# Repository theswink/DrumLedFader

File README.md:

# DrumLedFader
flash LED's when hitting the drums and do some more eye candy.

https://www.youtube.com/watch?v=Rv88M1jl1K8&t=31s&ab_channel=WilfredSwinkels

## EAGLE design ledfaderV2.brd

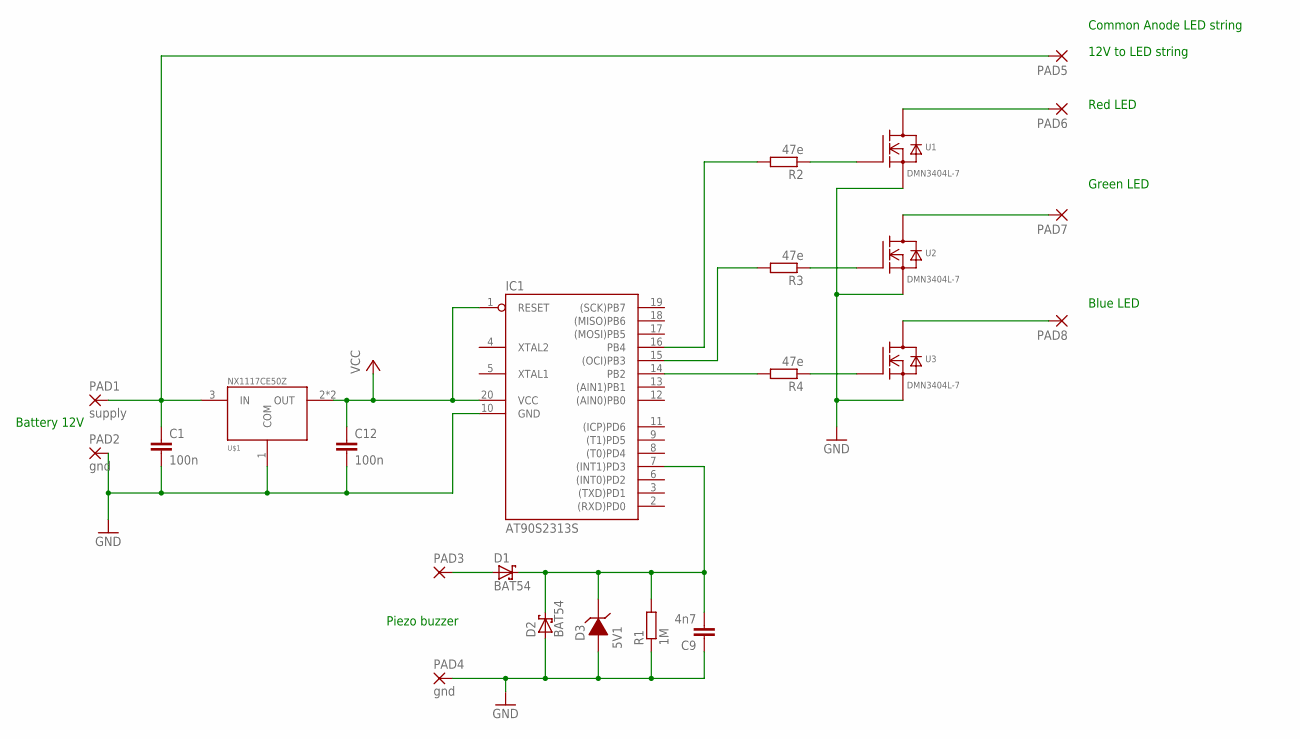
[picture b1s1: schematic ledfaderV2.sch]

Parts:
C1, C12: 100n; C1206
C9: 4n7; C1206
D1, D2: BAT54; SOT23
D3: 5V1; MINI-MELF
IC1: AT90S2313S; SO20L
PAD1: supply; SMD2,54-5,08
PAD2, PAD4: gnd; SMD2,54-5,08
PAD3, PAD5, PAD6, PAD7, PAD8: SMD5; SMD2,54-5,08
R1: 1M; M1206
R2, R3, R4: 47e; M1206
U1, U2, U3: DMN3404L-7; SOT95P235X112-3N; MPN DMN3404L-7
U$1: NX1117CE50Z; SOT223

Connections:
GND: C9.1, D2.1 (A), D3.1 (A), PAD4.1, R1.1, U1.2 (S), U2.2 (S), U3.2 (S)
unnamed: C1.1, PAD1.1, PAD5.1, U$1.3 (IN)
unnamed: C9.2, D1.3 (C), D2.3 (C), D3.2 (C), IC1.7 ((INT1)PD3), R1.2
unnamed: PAD6.1, U1.3 (D)
unnamed: PAD7.1, U2.3 (D)
unnamed: D1.1 (A), PAD3.1
unnamed: PAD8.1, U3.3 (D)
unnamed: R2.1, U1.1 (G)
unnamed: C1.2, C12.2, IC1.10 (GND), PAD2.1, U$1.1 (COM)
unnamed: R3.1, U2.1 (G)
unnamed: IC1.16 (PB4), R2.2
unnamed: IC1.15 ((OCI)PB3), R3.2
unnamed: IC1.14 (PB2), R4.2
unnamed: R4.1, U3.1 (G)
VCC: C12.1, IC1.1 (RESET), IC1.20 (VCC), U$1.2 (OUT), U$1.4 (OUT)

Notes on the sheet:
Battery 12V
12V to LED string
Red LED
Green LED
Blue LED
Common Anode LED string
Piezo buzzer

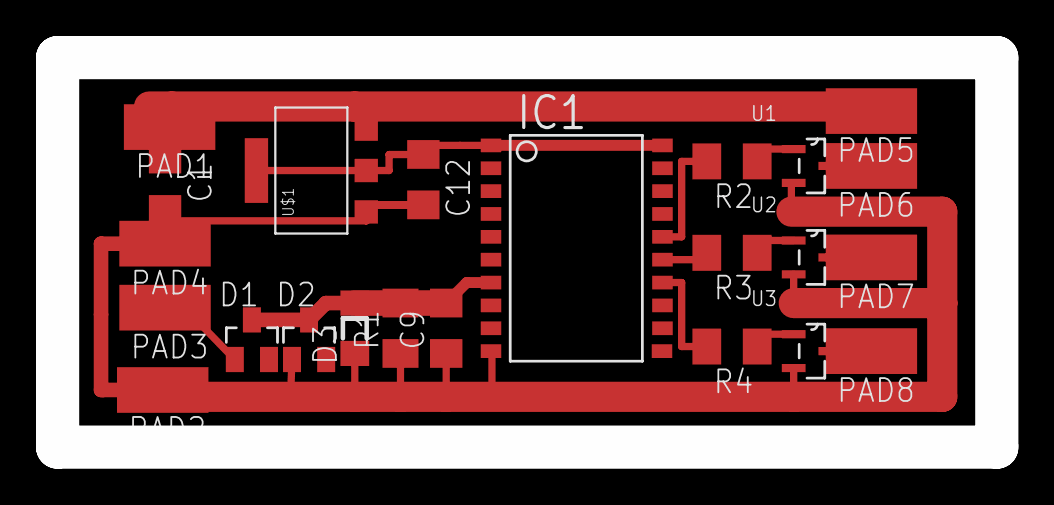
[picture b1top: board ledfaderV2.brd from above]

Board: 2 copper layers, 52.2 x 21.6 mm, 23 parts (0 on the bottom side), 15 nets.

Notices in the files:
parts and their libraries:
m-pad-2.1: License : GNU General Public License version 2 (see bottom)
